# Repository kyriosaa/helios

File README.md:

# Helios

A real-time lamp controller for my room. Keeps the time (even when unplugged) and flips a relay once the clock and alarm values match. 

My room doesn't have windows so I created this device to automatically turn on my bedside lamp and put myself into fight or flight every morning to help me wake up in time for work/school.

🎥 [Demo Video](https://youtu.be/W-aWS8Oxe-Q?si=ozM3OOpzgYfn5PJq) 🎥

| Sections |
| -------- |
| [Design](#design) |
| [Features](#features) |
| [Hardware](#hardware) |
| [PCB Design](#pcb-design) |
| [Schematic](#schematic) |
| [Images](#images) |

## Design

Some notes on why the board is built the way it is.

### A DS3231 instead of the MCU's own timer
The RTC has its own coin-cell backup, so the clock survives a power outage or being moved to another room. Keeping time on the MCU would mean re-setting the clock every time the device lost power, which is exactly the kind of small annoyance that would make me stop using it.

---

### Discrete multiplexing over a dedicated driver
A MAX7219 or TM1637 would have done this with fewer parts and less code. I used two 74HC595s for the segments and a 74HC138 plus PNP high-side drivers per display because I to practice building the multiplexing myself instead of buying it in a chip.

---

### A polled encoder, not an interrupt 
Every input has a 10k resistor and a 100nF capacitor on it to filter out switch bounce. The tradeoff to this is that signals now fade between HIGH and LOW over about a millisecond instead of snapping. During that fade, the Arduino can't really tell which one it's looking at, so a little noise makes it read HIGH-LOW-HIGH-LOW a few times before settling. An interrupt on `ENC_CLK` (D2) would count every one of those HIGH-LOW flips, so one click of the encoder knob would add 3 or 4 counts. However, reading the pin in the `loop()` function only ever sees the value after it settles, which solves the issue.

---

### Two board versions 
The 2-layer version is meant to be manually etched. But I know most people dont have an etching machine, so the 4-layer version is for anyone who doesn't have an etching setup and would rather send it to a manufacturer (I'm also experimenting with curved traces on the 4-layer version).

## Features

| Feature | Description |
| --- | --- |
| **24/7 Timekeeping** | A coin battery supports the DS3231, so pulling the plug doesn't require a manual time recalibration |
| **Dual Displays** | Separate 7-segment displays for the current time and alarm |
| **Manual Override** | One button forces the lamp on and disarms the alarm. The armed state is shown by a decimal point on the alarm display |
| **System ON/OFF** | Pressing the encoder blanks the displays and cuts the relay |
| **Multiplexed Digits** | Two 74HC595s (daisy-chained) drive segments, 74HC138s + PNP high-side drivers select digits |

## Hardware

| Ref | Qty | Part | Role |
| --- | --- | --- | --- |
| **A1** | 1 | Arduino Nano v3.x | MCU, socketed so it can be swapped without desoldering |
| **U1, U4** | 2 | 74HC595 | Daisy-chained shift registers driving the segment lines |
| **U2, U5** | 2 | 74HC138 | 3-to-8 decoders selecting which digit is lit |
| **U3, U6** | 2 | CA56-12EWA | Common-anode 4-digit 7-segment displays (time and alarm) |
| **Q1–Q8** | 8 | BC557 (PNP) | High-side drivers sourcing current into the selected digit |
| **SW1** | 1 | ALPS EC11E rotary encoder w/ switch | Sets values; pressing it toggles the system on/off |
| **SW2–SW4** | 3 | 6mm tactile push button | Mode, set, and manual lamp override |
| **J1** | 1 | JST-XH 1x03 | Relay / lamp output |
| **J2** | 1 | 1x04 pin socket | DS3231 RTC module (VCC, GND, SDA, SCL) |
| **R1–R6** | 6 | 10k | Pull-ups on the encoder and buttons |
| **R7–R10, R27–R30** | 8 | 1k | Base resistors for the PNP digit drivers |
| **R11–R26** | 16 | 330 | Segment current limiting |
| **C1–C8** | 8 | 100nF | Debounce caps on the inputs, paired with the 10k pull-ups |

Full parts list: [helios_bom.csv](./2layer/documents/helios_bom.csv)

## PCB Design

## Schematic

## Images

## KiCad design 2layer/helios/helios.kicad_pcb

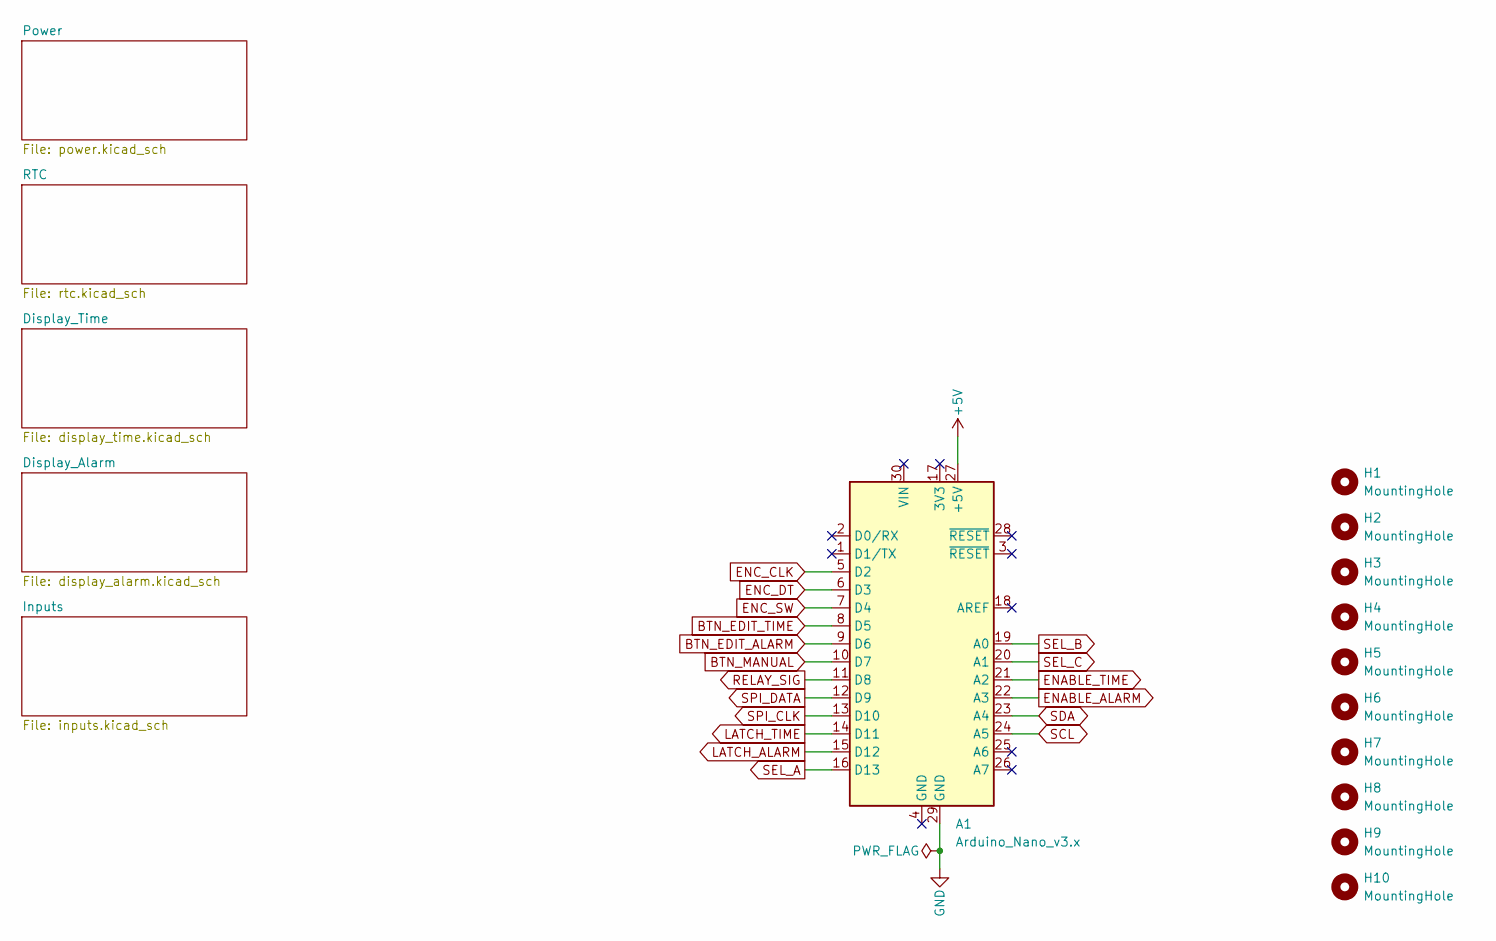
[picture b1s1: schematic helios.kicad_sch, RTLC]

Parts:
A1: Arduino_Nano_v3.x; Arduino_Nano
H1, H2, H3, H4, H9, H10: MountingHole; MountingHole_3.2mm_M3
H5: MountingHole; Relay_Module_5V_Mounting
H6, H7, H8: MountingHole

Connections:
+5V: A1.27 (+5V); also elsewhere on the board
BTN_EDIT_ALARM: A1.9 (D6); also elsewhere on the board
BTN_EDIT_TIME: A1.8 (D5); also elsewhere on the board
BTN_MANUAL: A1.10 (D7); also elsewhere on the board
ENABLE_ALARM: A1.22 (A3); also elsewhere on the board
ENABLE_TIME: A1.21 (A2); also elsewhere on the board
ENC_CLK: A1.5 (D2); also elsewhere on the board
ENC_DT: A1.6 (D3); also elsewhere on the board
ENC_SW: A1.7 (D4); also elsewhere on the board
GND: A1.29 (GND); also elsewhere on the board
LATCH_ALARM: A1.15 (D12); also elsewhere on the board
LATCH_TIME: A1.14 (D11); also elsewhere on the board
RELAY_SIG: A1.11 (D8); also elsewhere on the board
SCL: A1.24 (A5); also elsewhere on the board
SDA: A1.23 (A4); also elsewhere on the board
SEL_A: A1.16 (D13); also elsewhere on the board
SEL_B: A1.19 (A0); also elsewhere on the board
SEL_C: A1.20 (A1); also elsewhere on the board
SPI_CLK: A1.13 (D10); also elsewhere on the board
SPI_DATA: A1.12 (D9); also elsewhere on the board

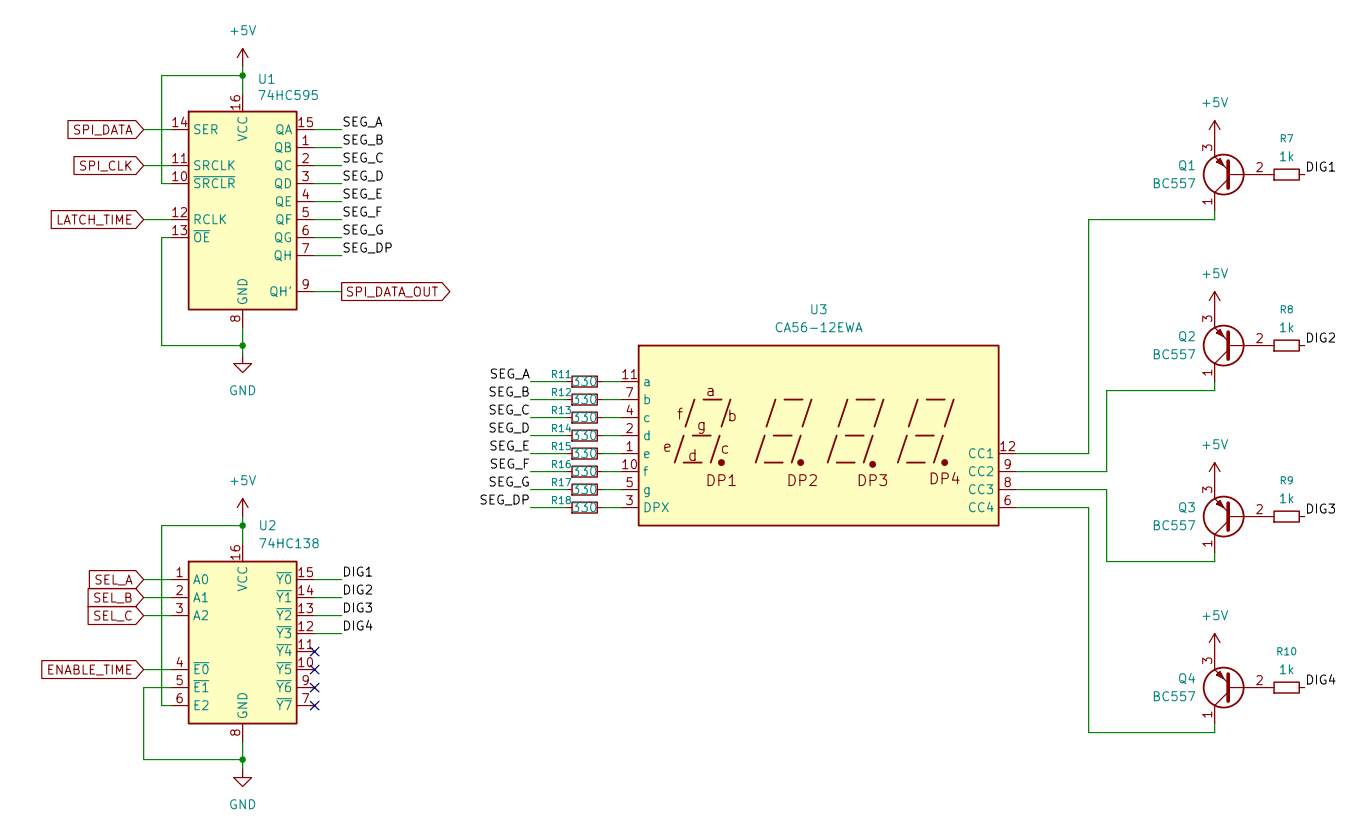
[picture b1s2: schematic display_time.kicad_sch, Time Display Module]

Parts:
Q1, Q2, Q3, Q4: BC557; TO-92_Inline_Wide
R7, R8, R9, R10: 1k; R_Axial_DIN0207_L6.3mm_D2.5mm_P7.62mm_Horizontal
R11, R12, R13, R14, R15, R16, R17, R18: 330; R_Axial_DIN0207_L6.3mm_D2.5mm_P7.62mm_Horizontal
U1: 74HC595; DIP-16_W7.62mm
U2: 74HC138; DIP-16_W7.62mm
U3: CA56-12EWA

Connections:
+5V: Q1.3 (E), Q2.3 (E), Q3.3 (E), Q4.3 (E), U1.10 (~SRCLR), U1.16 (VCC), U2.6 (E2), U2.16 (VCC); also elsewhere on the board
/Display_Time/DIG1: R7.2, U2.15 (~Y0)
/Display_Time/DIG2: R8.2, U2.14 (~Y1)
/Display_Time/DIG3: R9.2, U2.13 (~Y2)
/Display_Time/DIG4: R10.2, U2.12 (~Y3)
/Display_Time/SEG_A: R11.1, U1.15 (QA)
/Display_Time/SEG_B: R12.1, U1.1 (QB)
/Display_Time/SEG_C: R13.1, U1.2 (QC)
/Display_Time/SEG_D: R14.1, U1.3 (QD)
/Display_Time/SEG_DP: R18.1, U1.7 (QH)
/Display_Time/SEG_E: R15.1, U1.4 (QE)
/Display_Time/SEG_F: R16.1, U1.5 (QF)
/Display_Time/SEG_G: R17.1, U1.6 (QG)
ENABLE_TIME: U2.4 (~E0); also elsewhere on the board
GND: U1.8 (GND), U1.13 (~OE), U2.5 (~E1), U2.8 (GND); also elsewhere on the board
LATCH_TIME: U1.12 (RCLK); also elsewhere on the board
unnamed: Q1.2 (B), R7.1
unnamed: Q1.1 (C), U3.12 (CC1)
unnamed: Q2.2 (B), R8.1
unnamed: Q2.1 (C), U3.9 (CC2)
unnamed: Q3.2 (B), R9.1
unnamed: Q3.1 (C), U3.8 (CC3)
unnamed: Q4.2 (B), R10.1
unnamed: Q4.1 (C), U3.6 (CC4)
unnamed: R18.2, U3.3 (DPX)
unnamed: R11.2, U3.11 (a)
unnamed: R12.2, U3.7 (b)
unnamed: R13.2, U3.4 (c)
unnamed: R14.2, U3.2 (d)
unnamed: R15.2, U3.1 (e)
unnamed: R16.2, U3.10 (f)
unnamed: R17.2, U3.5 (g)
SEL_A: U2.1 (A0); also elsewhere on the board
SEL_B: U2.2 (A1); also elsewhere on the board
SEL_C: U2.3 (A2); also elsewhere on the board
SPI_CLK: U1.11 (SRCLK); also elsewhere on the board
SPI_DATA: U1.14 (SER); also elsewhere on the board
SPI_DATA_OUT: U1.9 (QH'); also elsewhere on the board

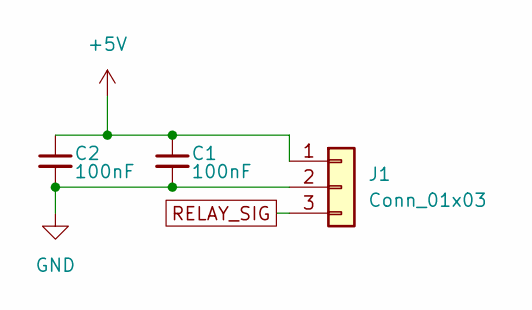
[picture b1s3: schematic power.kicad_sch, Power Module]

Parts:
C1, C2: 100nF; C_Disc_D5.0mm_W2.5mm_P2.50mm
J1: Conn_01x03; JST_XH_B3B-XH-A_1x03_P2.50mm_Vertical

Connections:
+5V: C1.1, C2.1, J1.1; also elsewhere on the board
GND: C1.2, C2.2, J1.2; also elsewhere on the board
RELAY_SIG: J1.3; also elsewhere on the board

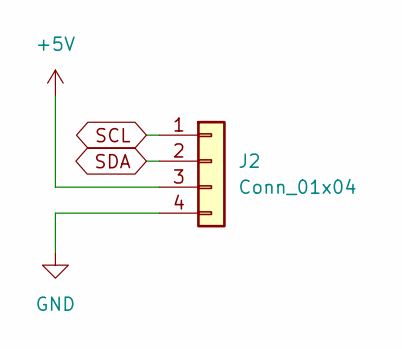
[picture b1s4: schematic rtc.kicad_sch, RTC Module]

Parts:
J2: Conn_01x04; PinSocket_1x04_P2.54mm_Vertical

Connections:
+5V: J2.3; also elsewhere on the board
GND: J2.4; also elsewhere on the board
SCL: J2.1; also elsewhere on the board
SDA: J2.2; also elsewhere on the board

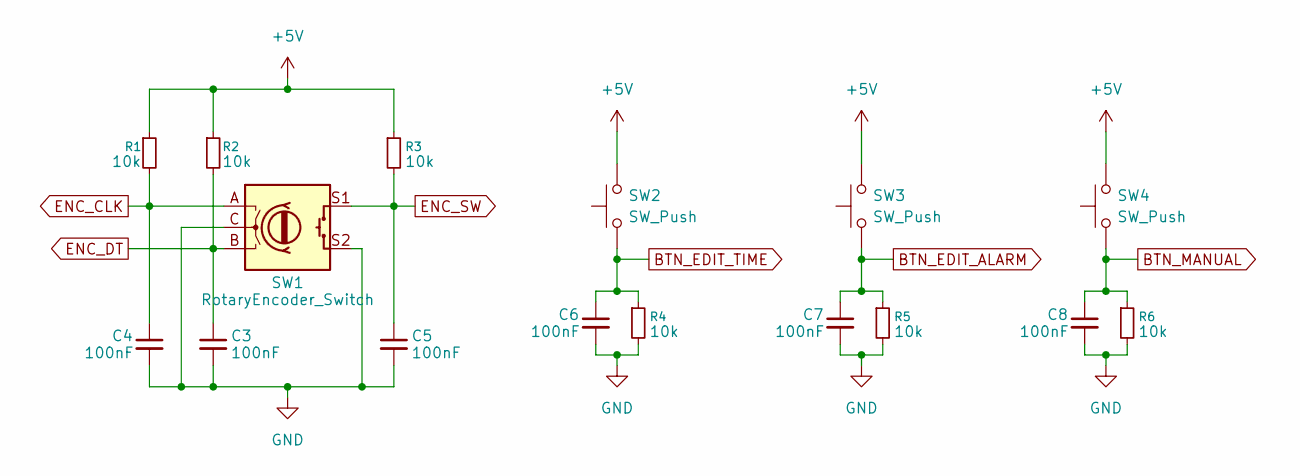
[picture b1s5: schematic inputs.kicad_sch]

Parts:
C3, C4, C5, C6, C7, C8: 100nF; C_Disc_D5.0mm_W2.5mm_P2.50mm
R1, R2, R3, R4, R5, R6: 10k; R_Axial_DIN0207_L6.3mm_D2.5mm_P7.62mm_Horizontal
SW1: RotaryEncoder_Switch; RotaryEncoder_Alps_EC11E-Switch_Vertical_H20mm
SW2, SW3, SW4: SW_Push; SW_PUSH_6mm

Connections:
+5V: R1.1, R2.1, R3.1, SW2.2, SW3.2, SW4.2; also elsewhere on the board
BTN_EDIT_ALARM: C7.1, R5.1, SW3.1; also elsewhere on the board
BTN_EDIT_TIME: C6.1, R4.1, SW2.1; also elsewhere on the board
BTN_MANUAL: C8.1, R6.1, SW4.1; also elsewhere on the board
ENC_CLK: C4.1, R1.2, SW1.A; also elsewhere on the board
ENC_DT: C3.1, R2.2, SW1.B; also elsewhere on the board
ENC_SW: C5.1, R3.2, SW1.S1; also elsewhere on the board
GND: C3.2, C4.2, C5.2, C6.2, C7.2, C8.2, R4.2, R5.2, R6.2, SW1.C, SW1.S2; also elsewhere on the board

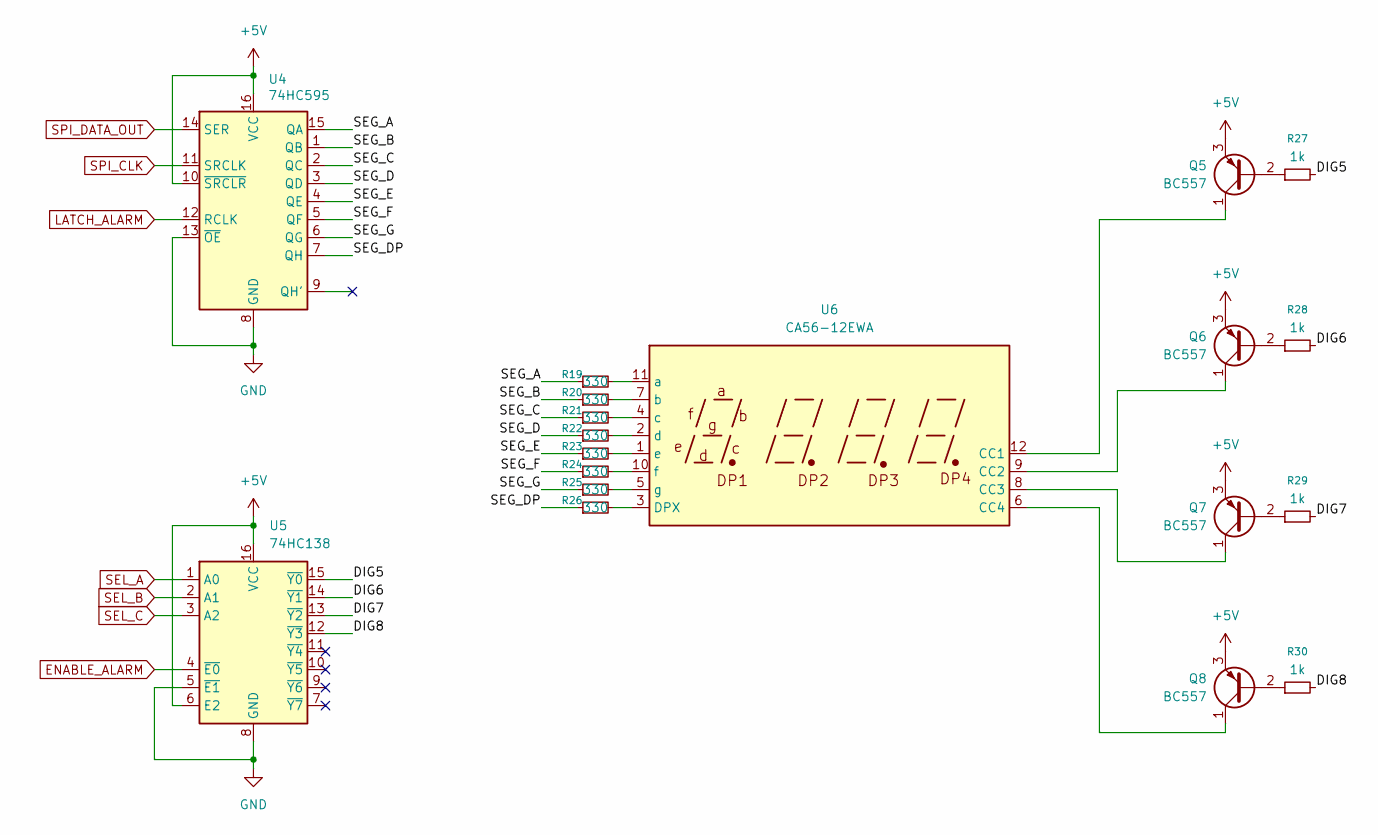
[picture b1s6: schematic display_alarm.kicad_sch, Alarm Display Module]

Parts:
Q5, Q6, Q7, Q8: BC557; TO-92_Inline_Wide
R19, R20, R21, R22, R23, R24, R25, R26: 330; R_Axial_DIN0207_L6.3mm_D2.5mm_P7.62mm_Horizontal
R27, R28, R29, R30: 1k; R_Axial_DIN0207_L6.3mm_D2.5mm_P7.62mm_Horizontal
U4: 74HC595; DIP-16_W7.62mm
U5: 74HC138; DIP-16_W7.62mm
U6: CA56-12EWA

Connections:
+5V: Q5.3 (E), Q6.3 (E), Q7.3 (E), Q8.3 (E), U4.10 (~SRCLR), U4.16 (VCC), U5.6 (E2), U5.16 (VCC); also elsewhere on the board
/Display_Alarm/DIG5: R27.2, U5.15 (~Y0)
/Display_Alarm/DIG6: R28.2, U5.14 (~Y1)
/Display_Alarm/DIG7: R29.2, U5.13 (~Y2)
/Display_Alarm/DIG8: R30.2, U5.12 (~Y3)
/Display_Alarm/SEG_A: R19.1, U4.15 (QA)
/Display_Alarm/SEG_B: R20.1, U4.1 (QB)
/Display_Alarm/SEG_C: R21.1, U4.2 (QC)
/Display_Alarm/SEG_D: R22.1, U4.3 (QD)
/Display_Alarm/SEG_DP: R26.1, U4.7 (QH)
/Display_Alarm/SEG_E: R23.1, U4.4 (QE)
/Display_Alarm/SEG_F: R24.1, U4.5 (QF)
/Display_Alarm/SEG_G: R25.1, U4.6 (QG)
ENABLE_ALARM: U5.4 (~E0); also elsewhere on the board
GND: U4.8 (GND), U4.13 (~OE), U5.5 (~E1), U5.8 (GND); also elsewhere on the board
LATCH_ALARM: U4.12 (RCLK); also elsewhere on the board
unnamed: Q5.2 (B), R27.1
unnamed: Q5.1 (C), U6.12 (CC1)
unnamed: Q6.2 (B), R28.1
unnamed: Q6.1 (C), U6.9 (CC2)
unnamed: Q7.2 (B), R29.1
unnamed: Q7.1 (C), U6.8 (CC3)
unnamed: Q8.2 (B), R30.1
unnamed: Q8.1 (C), U6.6 (CC4)
unnamed: R26.2, U6.3 (DPX)
unnamed: R19.2, U6.11 (a)
unnamed: R20.2, U6.7 (b)
unnamed: R21.2, U6.4 (c)
unnamed: R22.2, U6.2 (d)
unnamed: R23.2, U6.1 (e)
unnamed: R24.2, U6.10 (f)
unnamed: R25.2, U6.5 (g)
SEL_A: U5.1 (A0); also elsewhere on the board
SEL_B: U5.2 (A1); also elsewhere on the board
SEL_C: U5.3 (A2); also elsewhere on the board
SPI_CLK: U4.11 (SRCLK); also elsewhere on the board
SPI_DATA_OUT: U4.14 (SER); also elsewhere on the board

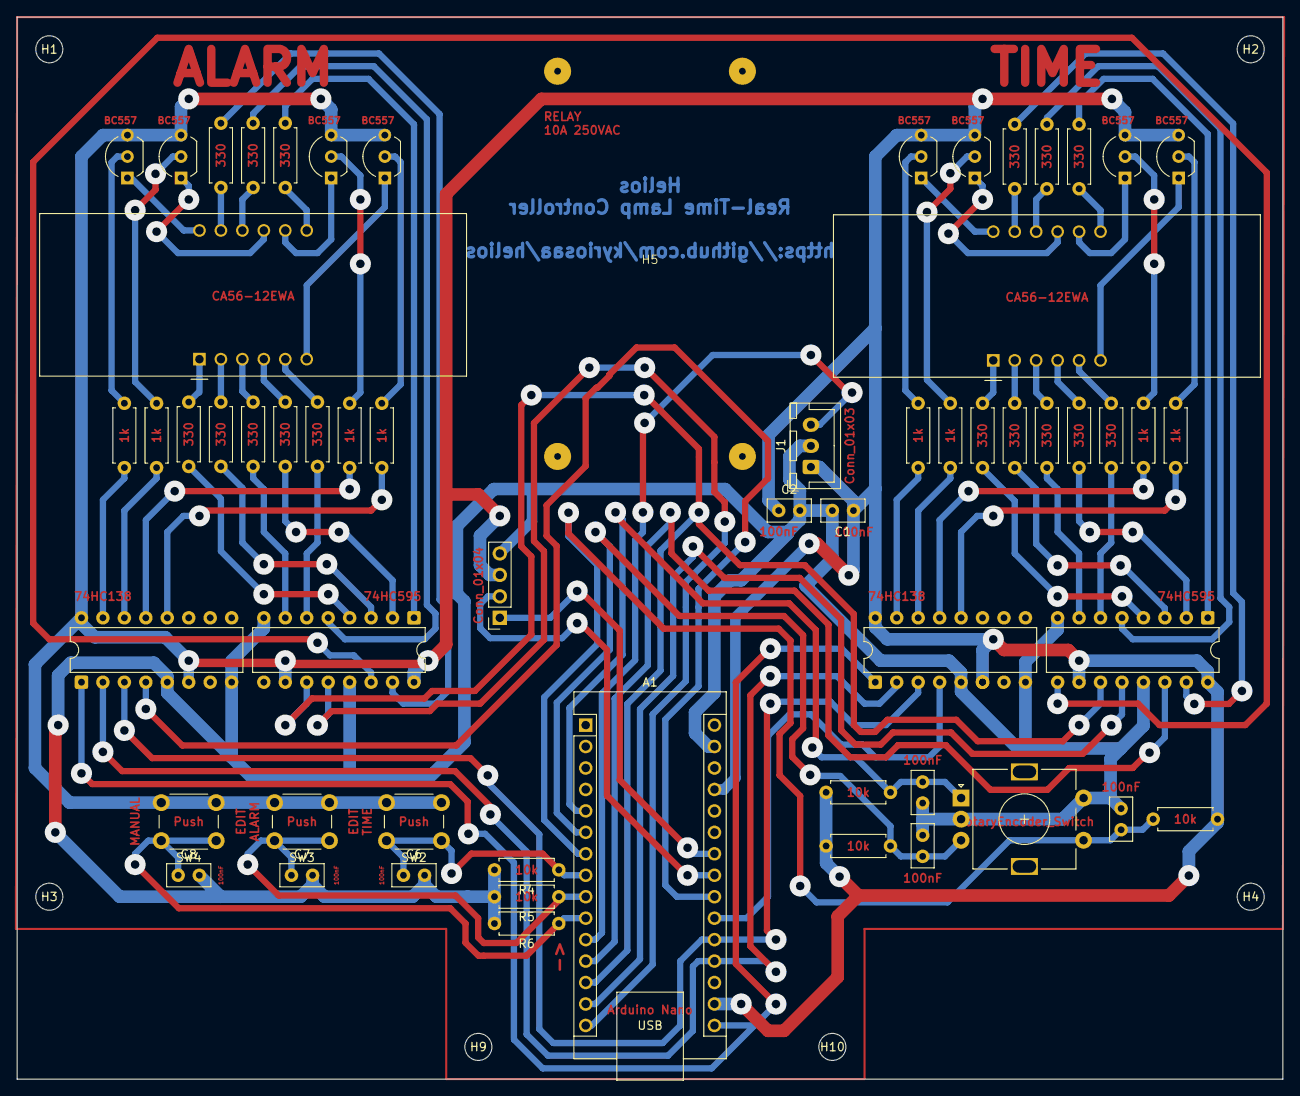
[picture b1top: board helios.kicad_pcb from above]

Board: 2 copper layers, 149.9 x 125.7 mm, 66 parts (0 on the bottom side), 77 nets.

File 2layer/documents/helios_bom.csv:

"Reference","Qty","Value","DNP","Exclude from BOM","Exclude from Board","Footprint","Datasheet"
"A1","1","Arduino_Nano_v3.x","","","","Module:Arduino_Nano","http://www.mouser.com/pdfdocs/Gravitech_Arduino_Nano3_0.pdf"
"C1,C2,C3,C4,C5,C6,C7,C8","8","100nF","","","","Capacitor_THT:C_Disc_D5.0mm_W2.5mm_P2.50mm",""
"J1","1","Conn_01x03","","","","Connector_JST:JST_XH_B3B-XH-A_1x03_P2.50mm_Vertical",""
"J2","1","Conn_01x04","","","","Connector_PinSocket_2.54mm:PinSocket_1x04_P2.54mm_Vertical",""
"Q1,Q2,Q3,Q4,Q5,Q6,Q7,Q8","8","BC557","","","","Package_TO_SOT_THT:TO-92_Inline_Wide","https://www.onsemi.com/pub/Collateral/BC556BTA-D.pdf"
"R1,R2,R3,R4,R5,R6","6","10k","","","","Resistor_THT:R_Axial_DIN0207_L6.3mm_D2.5mm_P7.62mm_Horizontal",""
"R7,R8,R9,R10,R27,R28,R29,R30","8","1k","","","","Resistor_THT:R_Axial_DIN0207_L6.3mm_D2.5mm_P7.62mm_Horizontal",""
"R11,R12,R13,R14,R15,R16,R17,R18,R19,R20,R21,R22,R23,R24,R25,R26","16","330","","","","Resistor_THT:R_Axial_DIN0207_L6.3mm_D2.5mm_P7.62mm_Horizontal",""
"SW1","1","RotaryEncoder_Switch","","","","Rotary_Encoder:RotaryEncoder_Alps_EC11E-Switch_Vertical_H20mm",""
"SW2,SW3,SW4","3","SW_Push","","","","Button_Switch_THT:SW_PUSH_6mm",""
"U1,U4","2","74HC595","","","","Package_DIP:DIP-16_W7.62mm","http://www.ti.com/lit/ds/symlink/sn74hc595.pdf"
"U2,U5","2","74HC138","","","","Package_DIP:DIP-16_W7.62mm","http://www.ti.com/lit/ds/symlink/cd74hc238.pdf"
"U3,U6","2","CA56-12EWA","","","","Display_7Segment:CA56-12EWA","http://www.kingbrightusa.com/images/catalog/SPEC/CA56-12EWA.pdf"

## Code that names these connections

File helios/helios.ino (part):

#include <Wire.h>
#include <EEPROM.h>

const uint8_t PIN_ENC_CLK      = 2;   // D2
const uint8_t PIN_ENC_DT       = 3;   // D3
const uint8_t PIN_ENC_SW       = 4;   // D4, active LOW (pull-up on board)
const uint8_t PIN_BTN_TIME     = 5;   // D5, active HIGH (pull-down on board)
const uint8_t PIN_BTN_ALARM    = 6;   // D6, active HIGH
const uint8_t PIN_BTN_MANUAL   = 7;   // D7, active HIGH
const uint8_t PIN_RELAY        = 8;   // D8 -> relay module signal
const uint8_t PIN_SPI_DATA     = 9;   // D9  -> U1 SER (chained into U4)
const uint8_t PIN_SPI_CLK      = 10;  // D10 -> both 595 SRCLK
const uint8_t PIN_LATCH_TIME   = 11;  // D11 -> U1 RCLK
const uint8_t PIN_LATCH_ALARM  = 12;  // D12 -> U4 RCLK
const uint8_t PIN_SEL_A        = 13;  // D13 -> 138 A0
const uint8_t PIN_SEL_B        = A0;  //     -> 138 A1
const uint8_t PIN_SEL_C        = A1;  //     -> 138 A2
const uint8_t PIN_EN_TIME      = A2;  // 74HC138 enable, ACTIVE LOW
const uint8_t PIN_EN_ALARM     = A3;  // 74HC138 enable, ACTIVE LOW

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};
const uint8_t SEG_BLANK = 0x00;
const uint8_t SEG_DP    = 0x80;

// state
enum Mode : uint8_t {
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  static uint32_t lastStepMs = 0;
  int8_t step = 0;

  uint8_t clk = digitalRead(PIN_ENC_CLK);
  if (lastClk == HIGH && clk == LOW && (millis() - lastStepMs) > 3) {
    step = digitalRead(PIN_ENC_DT) ? +1 : -1;
#if ENCODER_REVERSED
    step = -step;
#endif
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Button buttons[] = {
  { PIN_BTN_TIME,   true,  false, false, 0, false },
  { PIN_BTN_ALARM,  true,  false, false, 0, false },
  { PIN_BTN_MANUAL, true,  false, false, 0, false },
  { PIN_ENC_SW,     false, false, false, 0, false },
};
enum { BTN_TIME, BTN_ALARM, BTN_MANUAL, BTN_POWER };

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  alarmByte = ~alarmByte;
  timeByte  = ~timeByte;
#endif
  shiftOut(PIN_SPI_DATA, PIN_SPI_CLK, MSBFIRST, alarmByte);
  shiftOut(PIN_SPI_DATA, PIN_SPI_CLK, MSBFIRST, timeByte);
  digitalWrite(PIN_LATCH_TIME, HIGH);
  digitalWrite(PIN_LATCH_ALARM, HIGH);
  digitalWrite(PIN_LATCH_TIME, LOW);
  digitalWrite(PIN_LATCH_ALARM, LOW);
}

void muxStep() {
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
  shiftBoth(SEG_BLANK, SEG_BLANK);          // drain the segment lines while blanked

  digitalWrite(PIN_SEL_A, phase & 1);
  digitalWrite(PIN_SEL_B, (phase >> 1) & 1);
  digitalWrite(PIN_SEL_C, LOW);

  shiftBoth(alarmBuf[phase], timeBuf[phase]);

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  Serial.println(F("HELIOS debug"));
#endif

  pinMode(PIN_ENC_CLK,     INPUT);
  pinMode(PIN_ENC_DT,      INPUT);
  pinMode(PIN_ENC_SW,      INPUT);
  pinMode(PIN_BTN_TIME,    INPUT);
  pinMode(PIN_BTN_ALARM,   INPUT);
  pinMode(PIN_BTN_MANUAL,  INPUT);

  pinMode(PIN_RELAY,       OUTPUT);
  pinMode(PIN_SPI_DATA,    OUTPUT);
  pinMode(PIN_SPI_CLK,     OUTPUT);
  pinMode(PIN_LATCH_TIME,  OUTPUT);
  pinMode(PIN_LATCH_ALARM, OUTPUT);
  pinMode(PIN_SEL_A,       OUTPUT);
  pinMode(PIN_SEL_B,       OUTPUT);
  pinMode(PIN_SEL_C,       OUTPUT);
  pinMode(PIN_EN_TIME,     OUTPUT);
  pinMode(PIN_EN_ALARM,    OUTPUT);

  relayWrite(false);
  digitalWrite(PIN_EN_TIME,  HIGH);   // displays off until first mux step
  digitalWrite(PIN_EN_ALARM, HIGH);
  digitalWrite(PIN_LATCH_TIME,  LOW);
  digitalWrite(PIN_LATCH_ALARM, LOW);

  Wire.begin();
  loadAlarm();
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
